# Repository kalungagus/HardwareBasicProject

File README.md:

# HardwareBasicProject
Projeto básico de Hardware com microcontroladores PIC32MZ

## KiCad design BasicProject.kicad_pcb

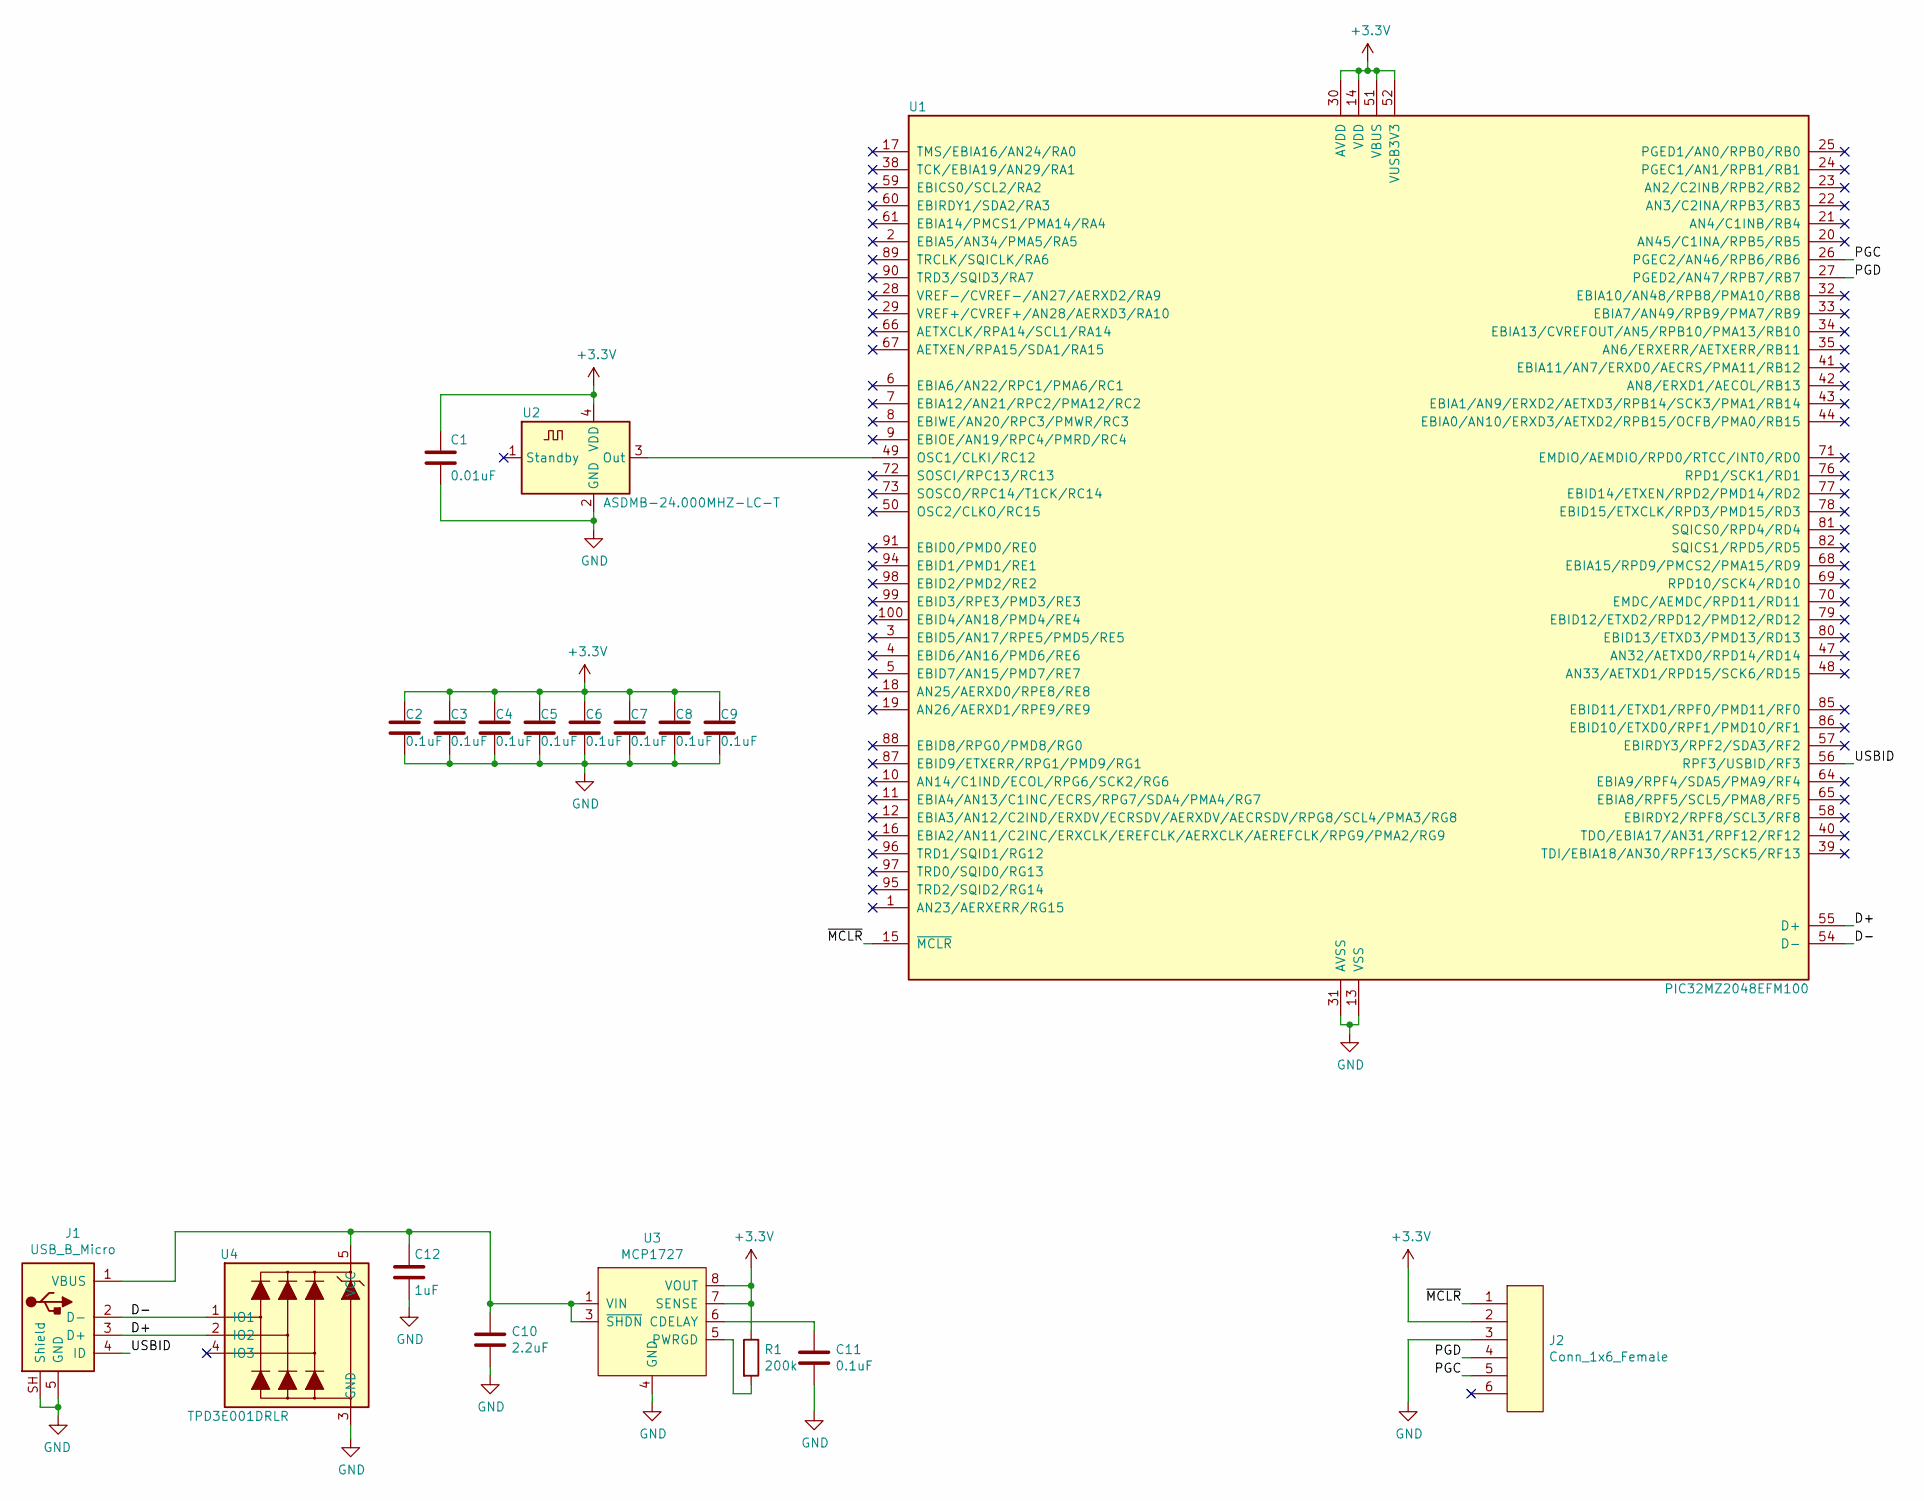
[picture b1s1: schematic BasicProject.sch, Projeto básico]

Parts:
C1: 0.01uF; C_0805
C2, C3, C4, C5, C6, C7, C8, C9, C11: 0.1uF; C_0805
C10: 2.2uF; C_0805
C12: 1uF; C_0805
J1: USB_B_Micro; Conn_USB_Amphenol_10118194-0001LF
J2: Conn_1x6_Female; PinHeader_1x06_P2.54mm_Vertical
R1: 200k; R_0805
U1: PIC32MZ2048EFM100; PIC32MZ_QFP-100_B14x14mm_P0.4mm
U2: ASDMB-24.000MHZ-LC-T; XTAL_ASDMB-24.000MHZ-LC-T
U3: MCP1727; Regulator_SOIC-8_B6x4.9mm_P1.27mm
U4: TPD3E001DRLR

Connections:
+3V3: C1.1, C2.1, C3.1, C4.1, C5.1, C6.1, C7.1, C8.1, C9.1, J2.2, R1.1, U1.14 (VDD), U1.30 (AVDD), U1.37 (VDD), U1.46 (VDD), U1.51 (VBUS), U1.52 (VUSB3V3), U1.62 (VDD), U1.74 (VDD), U1.83 (VDD), U1.93 (VDD), U2.4 (VDD), U3.7 (SENSE), U3.8 (VOUT)
/D+: J1.3 (D+), U1.55 (D+), U4.2 (IO2)
/D-: J1.2 (D-), U1.54 (D-), U4.1 (IO1)
/PGC: J2.5, U1.26 (PGEC2/AN46/RPB6/RB6)
/PGD: J2.4, U1.27 (PGED2/AN47/RPB7/RB7)
/USBID: J1.4 (ID), U1.56 (RPF3/USBID/RF3)
/~MCLR: J2.1, U1.15 (~MCLR)
GND: C1.2, C2.2, C3.2, C4.2, C5.2, C6.2, C7.2, C8.2, C9.2, C10.2, C11.2, C12.2, J1.5 (GND), J1.SH (Shield), J2.3, U1.13 (VSS), U1.31 (AVSS), U1.36 (VSS), U1.45 (VSS), U1.53 (VSS), U1.63 (VSS), U1.75 (VSS), U1.84 (VSS), U1.92 (VSS), U2.2 (GND), U3.4 (GND), U4.3 (GND)
unnamed: C11.1, U3.6 (CDELAY)
unnamed: R1.2, U3.5 (PWRGD)
unnamed: U1.49 (OSC1/CLKI/RC12), U2.3 (Out)
VIN: C10.1, C12.1, J1.1 (VBUS), U3.1 (VIN), U3.2 (VIN), U3.3 (~SHDN), U4.5 (VCC)

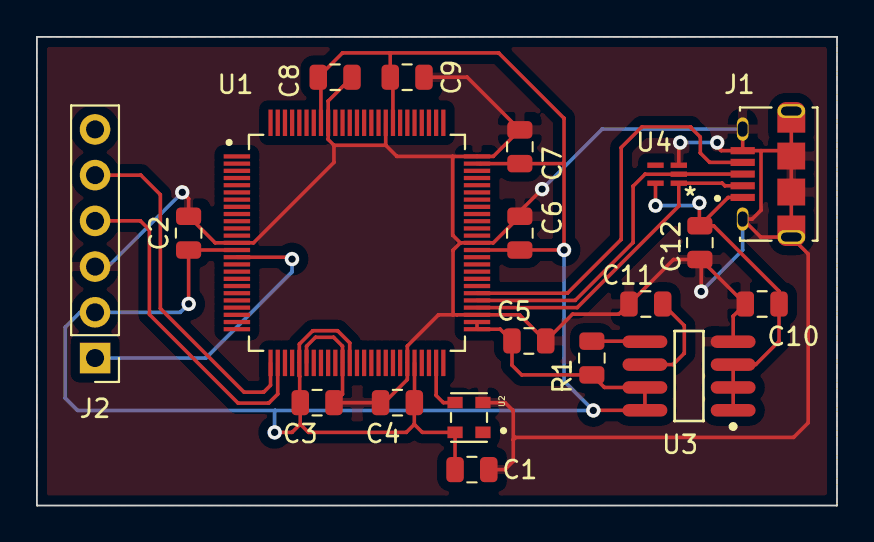
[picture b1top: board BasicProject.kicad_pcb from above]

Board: 2 copper layers, 44.5 x 26.0 mm, 19 parts (0 on the bottom side), 12 nets.

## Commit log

2020-07-07 Versão inicial do projeto
2020-07-25 Concluído o projeto básico para hardware

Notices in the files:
parts and their libraries:
Copyright 2016 Accelerated Designs. All rights reserved.
